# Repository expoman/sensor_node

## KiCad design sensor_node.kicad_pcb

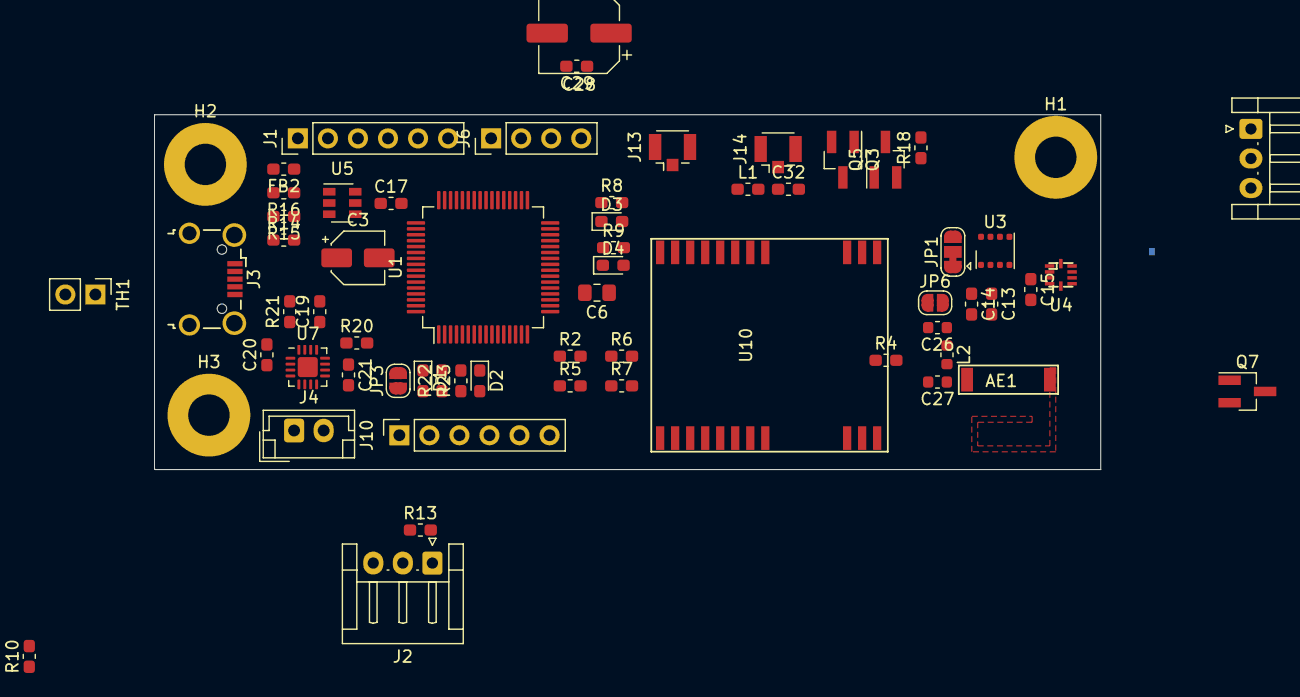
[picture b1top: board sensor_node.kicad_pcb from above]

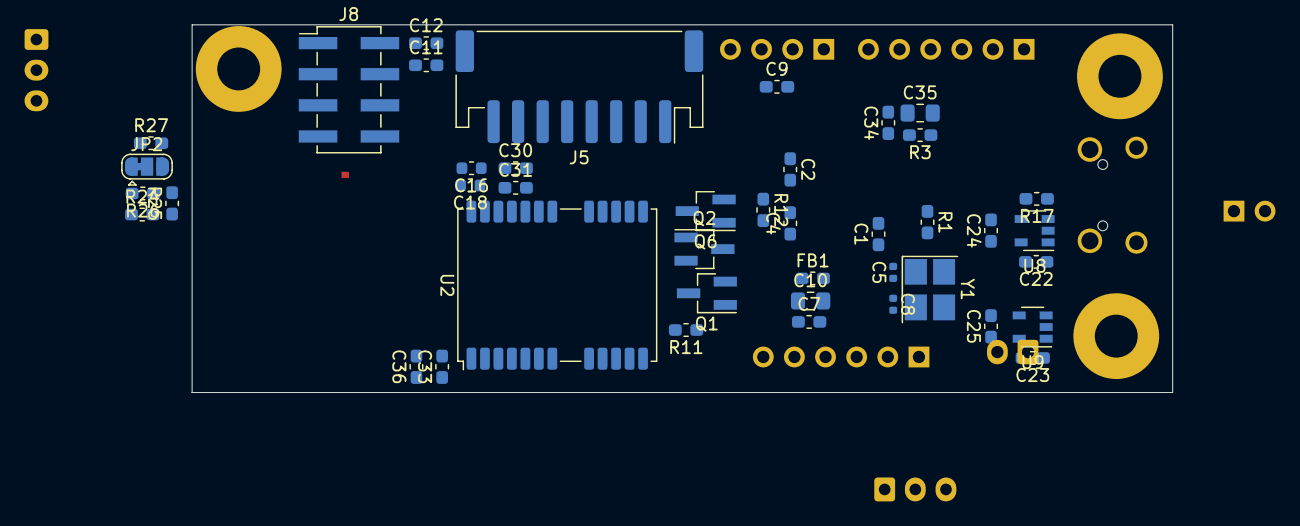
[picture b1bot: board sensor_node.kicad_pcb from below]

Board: 2 copper layers, 80.0 x 30.0 mm, 106 parts (42 on the bottom side), 73 nets, no tracks yet.

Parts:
AE1: Antenna_Chip; 0868AT43A0020
C1, C2, C4, C7, C11, C13, C14, C15, C29, C31, C34, C36: 100nF; C_0603_1608Metric_Pad1.05x0.95mm_HandSolder
C3: 10uF; CP_Elec_4x5.7
C5, C8: 10pF; C_0402_1005Metric
C6, C10, C35: 10uF; C_0805_2012Metric_Pad1.15x1.40mm_HandSolder
C9: 100nF; R_0603_1608Metric_Pad1.05x0.95mm_HandSolder
C12, C30, C33: 10uF; C_0603_1608Metric_Pad1.05x0.95mm_HandSolder
C16: 10uF; C_0603_1608Metric
C17: C; C_0603_1608Metric_Pad1.05x0.95mm_HandSolder
C18: 100nF; C_0603_1608Metric
C19, C22, C23, C24, C25: 1uF; C_0603_1608Metric_Pad1.05x0.95mm_HandSolder
C20, C21: 4.7uF; C_0603_1608Metric_Pad1.05x0.95mm_HandSolder
C26: 3.9pF; C_0603_1608Metric
C27: 0.3pF; C_0603_1608Metric
C28: 10uF; CP_Elec_6.3x3
C32: 2.2pf,25V; C_0603_1608Metric_Pad1.05x0.95mm_HandSolder
D1: LED_GREEN; LED_0603_1608Metric_Pad1.05x0.95mm_HandSolder
D2: LED_RED; LED_0603_1608Metric_Pad1.05x0.95mm_HandSolder
D3, D4: LED; LED_0603_1608Metric_Pad1.05x0.95mm_HandSolder
FB1, FB2: Ferrite_Bead; R_0603_1608Metric_Pad1.05x0.95mm_HandSolder
H1, H2, H3: MountingHole_Pad; MountingHole_3.5mm_Pad
J1: Conn_01x06_Male; PinHeader_1x06_P2.54mm_Vertical
J2, J9: Conn_01x03; JST_EH_S3B-EH_1x03_P2.50mm_Horizontal
J3: USB_B_Micro; USB_Micro-B_Wuerth_629105150521_CircularHoles
J4: Conn_01x02_Female; JST_EH_B2B-EH-A_1x02_P2.50mm_Vertical
J5: Conn_01x08_Male; JST_PH_S8B-PH-SM4-TB_1x08-1MP_P2.00mm_Horizontal
J6: Conn_01x04_Male; PinHeader_1x04_P2.54mm_Vertical
J8: Conn_02x04_Odd_Even; PinHeader_2x04_P2.54mm_Vertical_SMD
J10: Conn_01x06; PinSocket_1x06_P2.54mm_Vertical
J13, J14: Conn_Coaxial; U.FL_Hirose_U.FL-R-SMT-1_Vertical
JP1, JP2: SolderJumper_3_Bridged12; SolderJumper-3_P1.3mm_Bridged12_RoundedPad1.0x1.5mm
JP3: Jumper_2_Open; SolderJumper-2_P1.3mm_Open_RoundedPad1.0x1.5mm
JP6: SolderJumper_2_Open; SolderJumper-2_P1.3mm_Open_RoundedPad1.0x1.5mm
L1: 8.2nH,2%; L_0603_1608Metric_Pad1.05x0.95mm_HandSolder
L2: 18nH; L_0603_1608Metric
Q1: Q_NMOS_GSD; SOT-23_Handsoldering
Q2, Q3: Q_NMOS_DGS; SOT-23_Handsoldering
Q5, Q6, Q7: Q_PMOS_GSD; SOT-23_Handsoldering
R1, R10, R25: 10k; R_0603_1608Metric_Pad1.05x0.95mm_HandSolder
R2, R5, R6, R7: 4k7; R_0603_1608Metric_Pad1.05x0.95mm_HandSolder
R3, R4, R8, R9, R11: R; R_0603_1608Metric_Pad1.05x0.95mm_HandSolder
R12, R18: R_Small; R_0603_1608Metric_Pad1.05x0.95mm_HandSolder
R13, R17: 4.7k; R_0603_1608Metric_Pad1.05x0.95mm_HandSolder
R14: 100k; R_0603_1608Metric_Pad1.05x0.95mm_HandSolder
R15, R16: 0; R_0603_1608Metric_Pad1.05x0.95mm_HandSolder
R20: 1.18k; R_0603_1608Metric_Pad1.05x0.95mm_HandSolder
R21: 1.13k; R_0603_1608Metric_Pad1.05x0.95mm_HandSolder
R22, R23: 1k; R_0603_1608Metric_Pad1.05x0.95mm_HandSolder
R24: 5k; R_0603_1608Metric_Pad1.05x0.95mm_HandSolder
R26, R27: 47k; R_0603_1608Metric_Pad1.05x0.95mm_HandSolder
TH1: Thermistor_NTC; PinHeader_1x02_P2.54mm_Vertical
U1: STM32L063R8Tx; LQFP-64_10x10mm_P0.5mm
U2: NEO-M8Q; ublox_NEO
U3: BME680; Bosch_LGA-8_3x3mm_P0.8mm_ClockwisePinNumbering
U4: Si1133; DFN-10_NC2_2x2mm_P0.5mm
U5: USBLC6-2SC6; SOT-23-6
U7: BQ24075; QFN-16-1EP_3x3mm_P0.5mm_EP1.7x1.7mm
U8: LD39015M33R; SOT-23-5
U9: LD39015M18R; SOT-23-5
U10: E78-868LN22S; e22-868ln22s
Y1: Crystal_GND24; Crystal_SMD_TXC_7M-4Pin_3.2x2.5mm_HandSoldering

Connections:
/1WIRE0_EXT_DATA: J2.2, J9.2, R13.1
/DISP_DC: J5.6, U1.41
/DISP_RST: J5.7, U1.42
/EN_3V3: R17.2, U8.3
/ESP_RX: J8.8, U1.51
/ESP_TX: J8.1, U1.52
/GPS_RX: U1.58, U2.21
/GPS_SCL: J6.4, R2.1, U1.61, U2.19
/GPS_SDA: J6.2, R5.1, U1.62, U2.18
/GPS_TX: U1.59, U2.20
/I2C2_SCL: R6.1, U3.4, U4.2
/I2C2_SDA: R7.1, U3.3, U4.1
/LORA_RX: U1.17, U10.7
/LORA_TX: U1.16, U10.8
/PB1: J8.4, R10.2
/PC4: D2.1, J10.2, J10.3, U7.9
/PC5: D1.1, J10.4, U7.7
/PC13: R24.1, U4.4
/SPI1_MOSI: J5.3, U1.23
/SPI1_NSS: J5.5, U1.20
/SPI1_SCK: J5.4, U1.21
/VCC: C21.1, C22.1, C23.1, JP3.2, R17.1, U7.5, U7.10, U7.11, U8.1, U9.1, U9.3
/VCC_1V8: C1.1, C2.1, C4.1, C6.1, C25.1, FB1.2, J1.1, U1.19, U1.32, U1.64, U9.5
/VCC_3V3: C24.1, C28.1, C29.1, J2.1, J5.1, J6.1, J9.1, Q5.3, Q6.2, Q7.2, R2.2, R5.2, R6.2, R7.2, R12.1, R13.2, R18.1, U8.5, U10.10
/VUSB: C3.1, C17.1, C19.1, FB2.1, R3.1, U5.5, U7.13
/mcu.sch/NRST: C9.1, J1.5, U1.7
/mcu.sch/OSC_0: C5.1, U1.5, Y1.1
/mcu.sch/OSC_1: C8.1, U1.6, Y1.3
/mcu.sch/PA0: D3.2, U1.14
/mcu.sch/PA1: D4.2, U1.15
/mcu.sch/PA11: U1.44, U5.4
/mcu.sch/PA12: U1.45, U5.6
/mcu.sch/PA13: J1.4, U1.46
/mcu.sch/PA14: J1.2, U1.49
/mcu.sch/STM_VUSB: C34.1, C35.1, R3.2, R4.1, U1.48
/mcu.sch/VDDA: C7.1, C10.1, FB1.1, U1.13
/power_supply/TS: TH1.2, U7.1
/power_supply/VBAT: C20.1, J4.1, U7.2, U7.3
/sensors/GPS_TIMEPULSE: J13.1, U2.3
/sensors/VCC_SENSORS: C13.1, C14.1, C15.1, JP1.1, Q7.3, R24.2, R25.1, R26.1, U3.2, U3.6, U3.8, U4.3
/sensors/gps/GPS_VBCK: C16.1, C18.1, C30.1, C31.1, Q6.3, R11.2, U2.22, U2.23
/sensors/gps/VUSB: C33.1, C36.1, U2.7
/wireless/ANT_LORA: JP6.1, U10.21
/wireless/VCC_ESP: C11.1, C12.1, J8.2, Q5.2, R10.1
GND: C1.2, C2.2, C3.2, C4.2, C6.2, C7.2, C9.2, C10.2, C11.2, C12.2, C13.2, C14.2, C15.2, C16.2, C17.2, C18.2, C19.2, C20.2, C21.2, C22.2, C23.2, C24.2, C25.2, C26.2, C27.2, C28.2, C29.2, C30.2, C31.2, C32.2, C33.2, C34.2, C35.2, C36.2, H1.1, H2.1, H3.1, J1.3, J2.3, J3.5, J4.2, J5.2, J6.3, J8.7, J9.3, J13.2, J14.2, JP1.3, Q1.2, Q2.3, Q3.3, R1.2, R4.2, R8.2, R9.2, R14.2, R20.2, R21.2, R27.1, TH1.1, U1.12, U1.18, U1.31, U1.47, U1.63, U2.10, U2.12, U2.13, U2.24, U3.1, U3.7, U4.5, U4.8, U4.10, U5.2, U7.4, U7.6, U7.8, U7.14, U7.17, U8.2, U9.2, U10.1, U10.2, U10.3, U10.4, U10.11, U10.13, U10.19, U10.20, U10.22
unnamed: AE1.1, C27.1, L2.2
unnamed: C5.2, C8.2
unnamed: C26.1, JP6.2, L2.1
unnamed: C32.1, J14.1, L1.2
unnamed: D1.2, R22.2
unnamed: D2.2, R23.2
unnamed: D3.1, R8.1
unnamed: D4.1, R9.1
unnamed: FB2.2, J3.1
unnamed: J3.2, R16.2
unnamed: J3.3, R15.2
unnamed: J3.4, R14.1
unnamed: JP1.2, U3.5
unnamed: JP2.1, R26.2
unnamed: JP2.2, U4.6
unnamed: JP2.3, R27.2
unnamed: JP3.1, R22.1, R23.1
unnamed: L1.1, U2.11
unnamed: Q1.3, R11.1, U2.8
unnamed: Q2.1, Q6.1, R12.2
unnamed: Q3.1, Q5.1, R18.2
unnamed: R1.1, U1.60
unnamed: R15.1, U5.1
unnamed: R16.1, U5.3
unnamed: R20.1, U7.12
unnamed: R21.1, U7.16
unnamed: R25.2, U4.7, U4.9
unnamed: U10.12, U10.14, U10.15, U10.16, U10.17, U10.18

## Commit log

2020-01-16 add gitignore file
2020-01-16 add kicad files
2020-01-17 add new sheet for mcu
    changes to power-supply
2020-01-21 add esp12-f module
2020-01-24 add sensors and sensor connectors
    plus other stuff
2020-01-27 small changes
2020-01-27 add battery fuel gauge bq27441-g1 to project
2020-01-28 add interface pins to the sheets
    add usb bus
2020-01-28 update schematic
    - add footprints to all components
    - connect i2c channels
2020-02-04 replace lightsensor with si1133
    changes to several schematics like pins etc.
2020-02-05 add 1.8V power regulator and connected to mcu
2020-02-06 assign footprints
    replace polarity caps with unpol
2020-02-07 add footprint to tps826711
2020-02-07 add supply voltage 3.3V to sensor_connectors(1wire connector)
2020-02-07 resize mcu sheet
    connect esp uart interface
2020-02-07 added buses to mcu to connect to external periphery
2020-02-10 schematic work
2020-02-11 first update to pcb
2020-02-11 work on layout and smaller changes to schematic
2020-02-20 add missing fp-info-cache
2020-03-03 add more connectors(molex ezmate)
    change external i2c bus from i2c2 to i2c1
2020-03-04 - remove esp-12f module and add 6pin header for esp8266
    - add additional connector for external input => gpio pins
2020-03-06 changed stm32 mcu with newer stm32l552re
2020-03-09 updated mcu sheet to work with new stm32l5 mcu
2020-03-09 fix labels of lines
    update mcu with new interfaces
2020-03-10 changes sdcard socket
    connected mcu to sd card socket via sdio interface(4bit)
2020-03-11 added leds
    connected to timer outputs
2020-03-11 add can transceiver to mcu
2020-03-12 add gps module and started connecting
2020-03-13 add more to gps module
2020-03-16 change mosfets
    connect bus to stm32
    change connectors
2020-07-01 change mcu to smaller one
    change connectors
2020-07-02 strip of some components and use more external modules
2020-07-06 worked on board
2020-07-08 further work
2020-09-11 add docu
    more changes
